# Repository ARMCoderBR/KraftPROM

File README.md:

## Project

EEPROM Programmer

## Description

A Hardware + Software suite to program EEPROMs (28C16 and 28C64).

## Version & Date
1.0 - 2025-APR-24

## Author
Milton Maldonado Jr (ARM_Coder)

## License
GPL V2

## Target

PC Client Software: Any Linux with GCC

The repo for the PC client is here: https://github.com/ARMCoderBR/eeprom_sender

Firmware: Microchip PIC16F628A under MPLABX IDE 6.X and XC8 2.X (no PRO License
          needed). A suitable HEX file is already supplied for this PIC, so no
          IDE and compiler will be needed unless you will choose to use a
          different PIC.

## Hardware Materials
```
1  x  Universal PCB or Breadboard
1  x  PIC16F628A
3  x  74LS164 or HC164
1  x  74LS245 or HC245
1  x  74LS165 or HC165
1  x  ZIF Socket DIP 28 PIN
7  x  Ceramic Cap 100nF
2  x  Resistor 4k7
1  x  Jumper 3 pin
1  x  Molex 5 pin female
3  x  DIP 14 Socket (not needed for breadboard)
1  x  DIP 16 Socket   "     "    "      "
1  x  DIP 18 Socket   "     "    "      "
1  x  DIP 20 Socket   "     "    "      "
1  x  PC Serial-to-TTL adapter with 5V compatibility
1+ x  28C16 or 28C64 as target(s)

Wires, solder, etc.
```

See picture and schematics.

NOTE: 

## Equipment needed to Build and Program

PC
USB cables
Solder
Cutter and pliers
Multimeter
PIC programmer dongle (eg Pickit3)

## Building the Programmer

As said, if you have the recommended PIC16F628A, you can program it with the
supplied HEX file. This is the easiest way because you don't need to install
the complete MPLABX and the C compiler.

**You will still need a PIC programming tool, that most likely you won't have.
Since programming this PIC is a once in a lifetime event, you'd better borrow
the programmer from a friend or use the company's programmer when no one is looking...**

The rest of the build is a no-brainer, just be careful with the connections.
The Serial-to-TTL adapter is very practical, it supplies the power to the
hardware (5VDC) and the communication signals (TX/RX/CTS).

## Using the Programmer

All the control is done by the PC client software, as indicated above.

## Disclaimer

This project is supplied 'as is' with no warranty against bugs and errors.

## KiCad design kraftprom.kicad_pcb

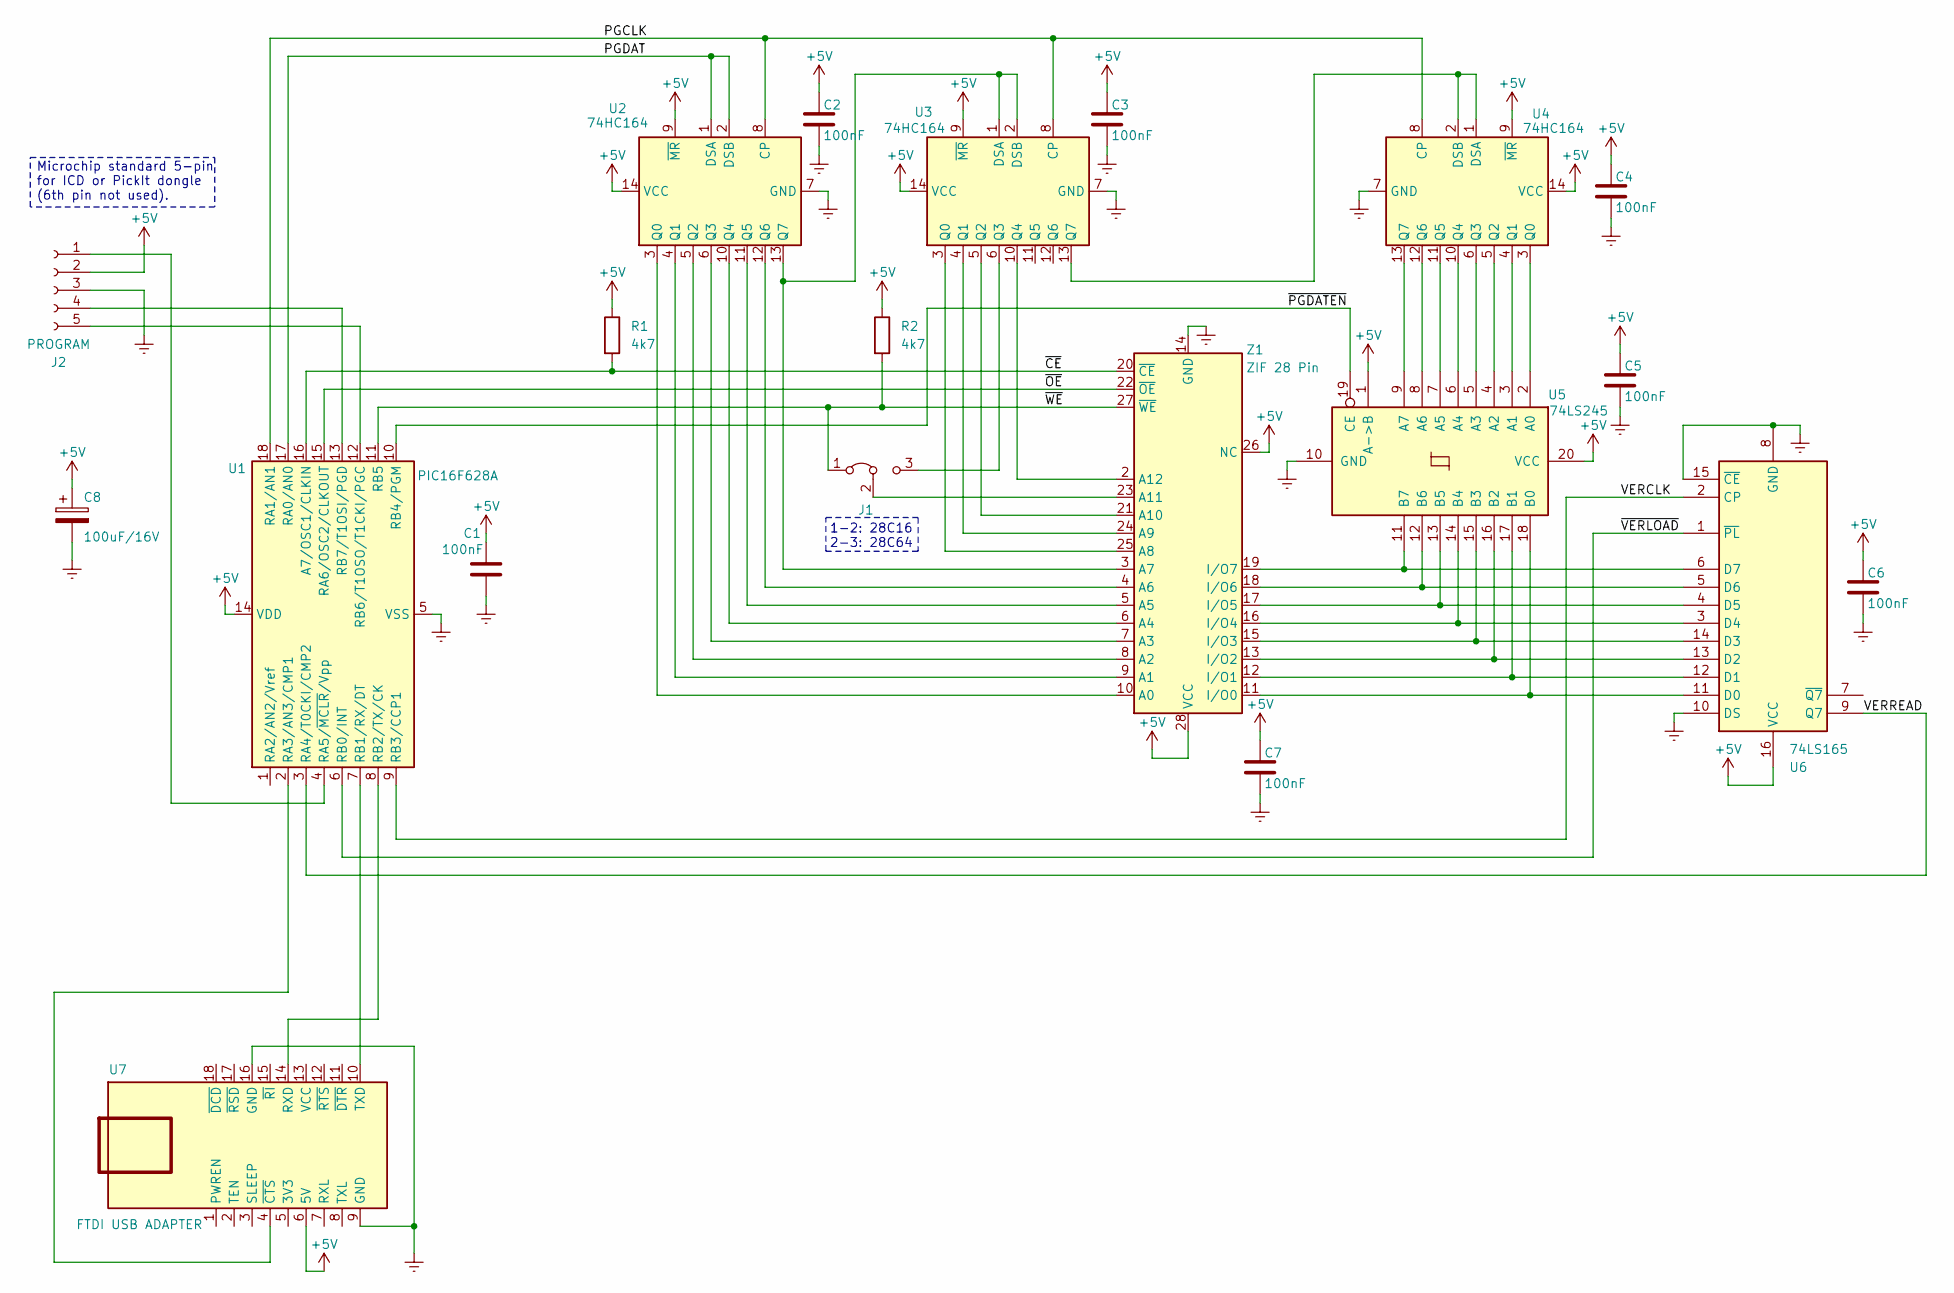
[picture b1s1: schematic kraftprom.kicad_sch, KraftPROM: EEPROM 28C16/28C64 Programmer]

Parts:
C1, C2, C3, C4, C5, C6, C7: 100nF
C8: 100uF/16V
J1: Jumper_3_Bridged12
J2: PROGRAM
R1, R2: 4k7
U1: PIC16F628A
U2, U3, U4: 74HC164
U5: 74LS245
U6: 74LS165
U7: FTDI USB ADAPTER
Z1: ZIF 28 Pin

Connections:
+5V: C1.1, C2.1, C3.1, C4.1, C5.1, C6.1, C7.1, C8.1, J2.2, R1.1, R2.1, U1.14 (VDD), U2.9 (~MR), U2.14 (VCC), U3.9 (~MR), U3.14 (VCC), U4.9 (~MR), U4.14 (VCC), U5.1 (A->B), U5.20 (VCC), U6.16 (VCC), U7.6 (5V), Z1.26 (NC), Z1.28 (VCC)
/PGCLK: U1.18 (RA1/AN1), U2.8 (CP), U3.8 (CP), U4.8 (CP)
/PGDAT: U1.17 (RA0/AN0), U2.1 (DSA), U2.2 (DSB)
/VERCLK: U1.9 (RB3/CCP1), U6.2 (CP)
/VERREAD: U1.3 (RA4/T0CKI/CMP2), U6.9 (Q7)
/~CE: R1.2, U1.16 (A7/OSC1/CLKIN), Z1.20 (~CE)
/~OE: U1.15 (RA6/OSC2/CLKOUT), Z1.22 (~OE)
/~PGDATEN: U1.10 (RB4/PGM), U5.19 (CE)
/~VERLOAD: U1.6 (RB0/INT), U6.1 (~PL)
/~WE: J1.1 (A), R2.2, U1.11 (RB5), Z1.27 (~WE)
Earth: C1.2, C2.2, C3.2, C4.2, C5.2, C6.2, C7.2, C8.2, J2.3, U1.5 (VSS), U2.7 (GND), U3.7 (GND), U4.7 (GND), U5.10 (GND), U6.8 (GND), U6.10 (DS), U6.15 (~CE), U7.9 (GND), U7.16 (GND), Z1.14 (GND)
unnamed: J1.3 (B), U3.6 (Q3)
unnamed: J1.2 (C), Z1.23 (A11)
unnamed: J2.1, U1.4 (RA5/~MCLR/Vpp)
unnamed: J2.4, U1.13 (RB7/T1OSI/PGD)
unnamed: J2.5, U1.12 (RB6/T1OSO/T1CKI/PGC)
unnamed: U1.2 (RA3/AN3/CMP1), U7.4 (~CTS)
unnamed: U1.7 (RB1/RX/DT), U7.10 (TXD)
unnamed: U1.8 (RB2/TX/CK), U7.14 (RXD)
unnamed: U2.3 (Q0), Z1.10 (A0)
unnamed: U2.4 (Q1), Z1.9 (A1)
unnamed: U2.5 (Q2), Z1.8 (A2)
unnamed: U2.6 (Q3), Z1.7 (A3)
unnamed: U2.10 (Q4), Z1.6 (A4)
unnamed: U2.11 (Q5), Z1.5 (A5)
unnamed: U2.12 (Q6), Z1.4 (A6)
unnamed: U2.13 (Q7), U3.1 (DSA), U3.2 (DSB), Z1.3 (A7)
unnamed: U3.3 (Q0), Z1.25 (A8)
unnamed: U3.4 (Q1), Z1.24 (A9)
unnamed: U3.5 (Q2), Z1.21 (A10)
unnamed: U3.10 (Q4), Z1.2 (A12)
unnamed: U3.13 (Q7), U4.1 (DSA), U4.2 (DSB)
unnamed: U4.3 (Q0), U5.2 (A0)
unnamed: U4.4 (Q1), U5.3 (A1)
unnamed: U4.5 (Q2), U5.4 (A2)
unnamed: U4.6 (Q3), U5.5 (A3)
unnamed: U4.10 (Q4), U5.6 (A4)
unnamed: U4.11 (Q5), U5.7 (A5)
unnamed: U4.12 (Q6), U5.8 (A6)
unnamed: U4.13 (Q7), U5.9 (A7)
unnamed: U5.18 (B0), U6.11 (D0), Z1.11 (I/O0)
unnamed: U5.17 (B1), U6.12 (D1), Z1.12 (I/O1)
unnamed: U5.16 (B2), U6.13 (D2), Z1.13 (I/O2)
unnamed: U5.15 (B3), U6.14 (D3), Z1.15 (I/O3)
unnamed: U5.14 (B4), U6.3 (D4), Z1.16 (I/O4)
unnamed: U5.13 (B5), U6.4 (D5), Z1.17 (I/O5)
unnamed: U5.12 (B6), U6.5 (D6), Z1.18 (I/O6)
unnamed: U5.11 (B7), U6.6 (D7), Z1.19 (I/O7)

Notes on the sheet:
1-2: 28C16 2-3: 28C64
Microchip standard 5-pin for ICD or PickIt dongle (6th pin not used).

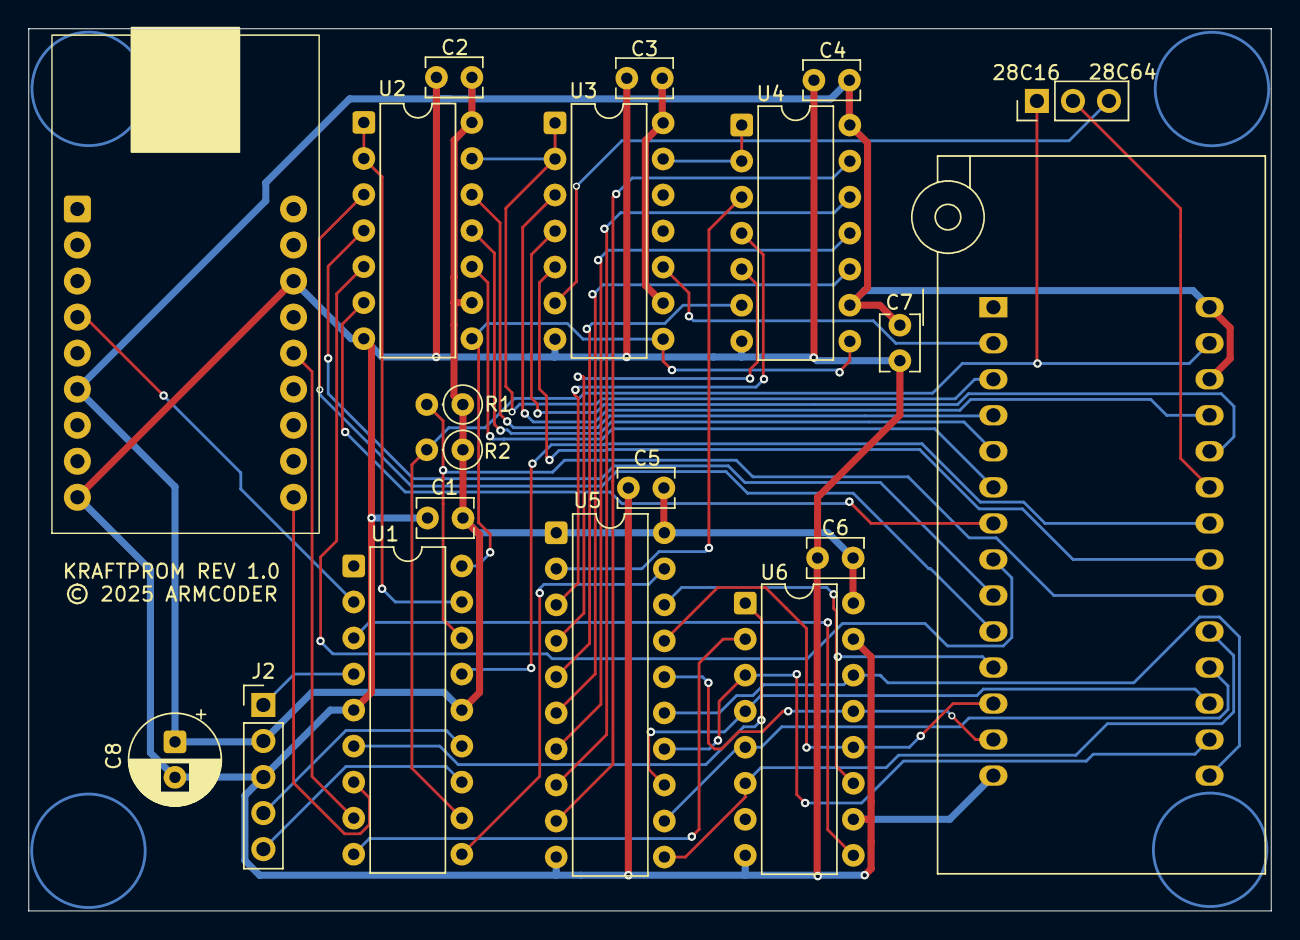
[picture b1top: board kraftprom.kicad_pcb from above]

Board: 2 copper layers, 87.6 x 62.2 mm, 20 parts (0 on the bottom side), 48 nets.

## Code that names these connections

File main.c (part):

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#define PGCLK_TRIS   TRISAbits.TRISA1
#define PGDAT_TRIS   TRISAbits.TRISA0
#define PGDATEN_TRIS TRISBbits.TRISB4
#define PGCLK        PORTAbits.RA1
#define PGDAT        PORTAbits.RA0
#define PGDATEN      PORTBbits.RB4

#define EECE_TRIS    TRISAbits.TRISA7
#define EEOE_TRIS    TRISAbits.TRISA6
#define EEWE_TRIS    TRISBbits.TRISB5
#define EECE         PORTAbits.RA7
#define EEOE         PORTAbits.RA6
#define EEWE         PORTBbits.RB5

#define VERCLK_TRIS  TRISBbits.TRISB3
#define VERLOAD_TRIS TRISBbits.TRISB0
#define VERREAD_TRIS TRISAbits.TRISA4
#define VERCLK       PORTBbits.RB3
#define VERLOAD      PORTBbits.RB0
#define VERREAD      PORTAbits.RA4


////////////////////////////////////////////////////////////////////////////////
void io_init(){
    
    PGCLK = 0;
    PGDAT = 0;
    PGCLK_TRIS = 0;
    PGDAT_TRIS = 0;
    PGDATEN = 1;
    PGDATEN_TRIS = 0;
    
    EECE = 1;
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    EEOE_TRIS = 0;
    EEWE_TRIS = 0;

    VERCLK = 0;
    VERLOAD = 1;
    VERCLK_TRIS = 0;
    VERLOAD_TRIS = 0;
    VERREAD_TRIS = 1;
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    for (i = 0; i < 8; i++){
        
        if (data & 0x80)
            PGDAT=1;
        else
            PGDAT=0;
        PGCLK=1;
        PGCLK=0;
        data <<= 1;
    }

    for (i = 0; i < 16; i++){
        
        if (addr & 0x8000)
            PGDAT=1;
        else
            PGDAT=0;
        PGCLK=1;
        PGCLK=0;
        addr <<= 1;
    }
}
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    EECE = 0;
    EEOE = 0;
    __delay_us(1);
    VERLOAD = 0;
    VERLOAD = 1;
    EEOE = 1;
    EECE = 1;
    
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            val |= msk;
        
        msk >>= 1;
        VERCLK = 1;
        VERCLK = 0;
        //__delay_us(1);
    }
    
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    
    send_addr_data(addr, data);

    PGDATEN = 0;
    __delay_us(1);
    EECE = 0;
    EEWE = 0;
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    EEWE = 1;
    EECE = 1;
    __delay_us(1);      // Hold Tdh
    PGDATEN = 1;

#if POLLED
    __delay_us(1);
    EECE = 0;
    EEOE = 0;
    __delay_us(1);
    VERLOAD = 0;
    VERLOAD = 1;
    EEOE = 1;
    EECE = 1;
    data >>= 7;
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        EECE = 0;
        EEOE = 0;
        __delay_us(1);
        VERLOAD = 0;
        VERLOAD = 1;
        EEOE = 1;
        EECE = 1;
        __delay_us(100);
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
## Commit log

2025-04-26 PIC acordou, falando com serial!
2025-04-29 Shift registers de entrada funcinando.
2025-04-29 Começando a ler a eeprom.
2025-04-29 Tentando gravar a eeprom.
2025-04-29 +Tentando gravar a eeprom.
2025-04-29 +Gravando a eeprom com parse de linhas INTEL Hex.
2025-04-30 Mais acertos.
2025-05-02 Limpando erro na primeira leitura após boot.
2025-05-07 Pequena otimização.
2025-05-07 Setting up files.
2025-05-07 Add picture.
2025-05-09 New READ function.
2025-05-09 Fix READ function.
2025-07-10 Minor schematic and picture updates.
2025-07-10 Update Hex file.
2025-09-16 KraftPROM
2025-09-16 More PCB design.
2025-09-16 More PCB design (fixes).
2025-09-17 More PCB design (clearances).
2025-10-13 More PCB fixes.

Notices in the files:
kraftprom.kicad_pcb:
© 2025 ARMCODER
kraftprom.kicad_sch:
(C) 2025 Milton Maldonado Jr (ARMCoder)
